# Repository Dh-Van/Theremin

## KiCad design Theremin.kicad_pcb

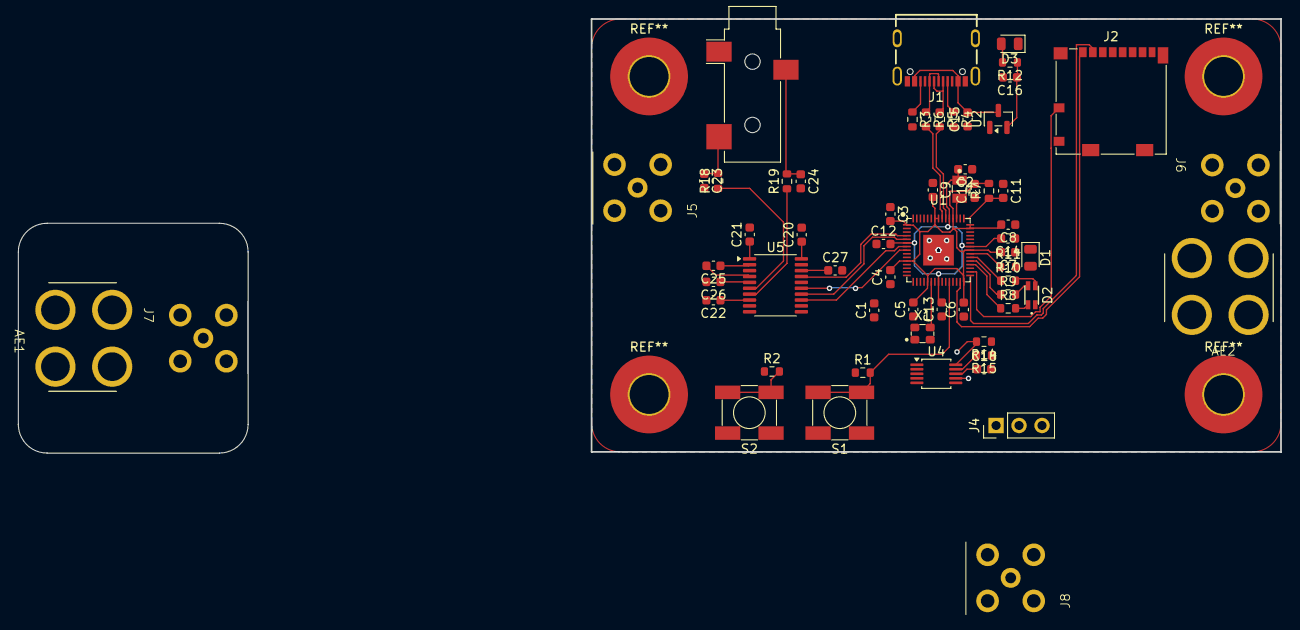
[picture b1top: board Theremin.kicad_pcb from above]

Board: 2 copper layers, 76.2 x 47.9 mm, 62 parts (0 on the bottom side), 54 nets.

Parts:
AE1: Pitch Input; Flat_Antenna_Mount
AE2: Volume Input; Flat_Antenna_Mount
C1, C2, C10, C11, C13: 4.7µF; C_0603_1608Metric
C3, C4, C5, C6, C7, C8, C9, C12, C14: 0.1µF; C_0603_1608Metric
C15, C16: 10µF; C_0603_1608Metric
C18, C27: 1uF; C_0603_1608Metric
C20, C21, C22: 10uF; C_0603_1608Metric
C23, C24: 2.2nF; C_0603_1608Metric
C25, C26: 2.2uF; C_0603_1608Metric
D1: LED; D_0805_2012Metric
D2: IN-S85TATRGB
D3: PWR; D_0805_2012Metric
J1: USB4105-GF-A
J2: Micro_SD_Card_Det2; microSD_HC_Molex_104031-0811
J4: DEBUG; PinHeader_1x03_P2.54mm_Vertical
J5, J6, J7, J8: Conn_Coaxial; Coax_Connector_Right_Angle
J9: AudioJack3; Jack_3.5mm_CUI_SJ-3523-SMT_Horizontal
L1: 3.3µH; AOTA-B201610S3R3-101-T
R1, R2, R3, R4, R9: 5.1K; R_0603_1608Metric
R5, R6: 27Ω; R_0603_1608Metric
R7: 33Ω; R_0603_1608Metric
R8, R10, R11, R12: 1K; R_0603_1608Metric
R14, R15: 3.7kΩ; R_0603_1608Metric
R18, R19: 470Ω; R_0603_1608Metric
S1: RST; TL3301AFxxxxJ
S2: BOOT; TL3301NFxxxxJ
U1: RP2354A; RP2350A_QFN-60_EP_7.75x7.75_Pitch0.4mm
U2: MCP1702T-3302E_CB; SOT-23
U4: FDC1004DGS; TSSOP-10_3x3mm_P0.5mm
U5: PCM5102A; TSSOP-20_4.4x6.5mm_P0.65mm
X1: IQXO-791_12MHz; IQXO-791

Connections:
+1V1: C2.2, C12.2, C13.2, C14.2, L1.1, U1.6 (DVDD), U1.23 (DVDD), U1.39 (DVDD), U1.50 (VREG_FB)
+3V3: C1.2, C3.2, C4.2, C5.2, C6.2, C7.2, C8.2, C9.2, C10.2, C16.1, C18.1, C20.1, C21.1, C22.1, D2.3, J2.4 (VDD), R1.1, R2.1, R7.2, R12.1, R14.1, R15.1, U1.1 (IOVDD), U1.11 (IOVDD), U1.20 (IOVDD), U1.30 (IOVDD), U1.38 (IOVDD), U1.44 (ADC_AVDD), U1.45 (IOVDD), U1.49 (VREG_VIN), U1.53 (USB_OTP_VDD), U1.54 (QSPI_IOVDD), U2.2 (VOUT), U4.8 (VDD), U5.1 (CPVDD), U5.8 (AVDD), U5.20 (DVDD), X1.4 (VS)
+5V: C15.2, J1.A4B9 (VBUS), J1.B4A9 (VBUS), U2.3 (VIN)
/Microcontroller/BOOT: R2.2, S2.2, U1.60 (~QSPI_CS)
/Microcontroller/GPIO14: J2.5 (CLK), U1.18 (GPIO14)
/Microcontroller/GPIO15: J2.3 (CMD), U1.19 (GPIO15)
/Microcontroller/GPIO16: J2.7 (DAT0), U1.27 (GPIO16)
/Microcontroller/GPIO17: J2.8 (DAT1), U1.28 (GPIO17)
/Microcontroller/GPIO18: J2.1 (DAT2), U1.29 (GPIO18)
/Microcontroller/GPIO19: J2.2 (DAT3/CD), U1.31 (GPIO19)
/Microcontroller/GPIO20: J2.9 (DET_B), U1.32 (GPIO20)
/Microcontroller/GPIO22: R8.1, U1.34 (GPIO22)
/Microcontroller/GPIO23: R9.1, U1.35 (GPIO23)
/Microcontroller/GPIO24: R10.1, U1.36 (GPIO24)
/Microcontroller/GPIO25: R11.1, U1.37 (GPIO25)
/Microcontroller/RUN: R1.2, S1.2, U1.26 (RUN)
/Microcontroller/SWCLK: J4.1, U1.24 (SWCLK)
/Microcontroller/SWDIO: J4.3, U1.25 (SWDIO)
GND: C1.1, C2.1, C3.1, C4.1, C5.1, C6.1, C7.1, C8.1, C9.1, C10.1, C11.1, C12.1, C13.1, C14.1, C15.1, C16.2, C18.2, C20.2, C21.2, C22.2, C23.2, C24.2, C26.2, C27.2, D1.1 (K), D3.1 (K), J1.A1B12 (GND), J1.B1A12 (GND), J1.S1 (SHELL), J1.S2 (SHELL), J1.S3 (SHELL), J1.S4 (SHELL), J2.6 (VSS), J2.10 (DET_A), J2.SH (SHIELD), J4.2, J9.S, R3.2, R4.2, S1.1, S2.1, U1.47 (VREG_PGND), U1.61 (GND), U2.1 (GND), U4.7 (GND), U5.3 (CPGND), U5.9 (AGND), U5.10 (DEMP), U5.11 (FLT), U5.12 (SCK), U5.16 (FMT), U5.19 (DGND), X1.2 (GND)
GNDREF: J7.2 (Ext), J8.2 (Ext)
GPIO2: U1.4 (GPIO2), U5.17 (XSMT)
GPIO3: U1.5 (GPIO3), U5.14 (DIN)
GPIO4: U1.7 (GPIO4), U5.13 (BCK)
GPIO5: U1.8 (GPIO5), U5.15 (LRCK)
GPIO6: R14.2, U1.9 (GPIO6), U4.10 (SDA)
GPIO7: R15.2, U1.10 (GPIO7), U4.9 (SCL)
unnamed: AE1.1 (A_1), J7.1 (In)
unnamed: AE2.1 (A_1), J8.1 (In)
unnamed: C23.1, J9.T, R18.2
unnamed: C24.1, J9.R, R19.2
unnamed: D1.2 (A), R11.2
unnamed: D2.1, R8.2
unnamed: D2.2, R9.2
unnamed: D2.4, R10.2
unnamed: D3.2 (A), R12.2
unnamed: J1.A5 (CC1), R4.1
unnamed: J1.B5 (CC2), R3.1
unnamed: J1.A6 (D+), J1.B6 (D+), R6.1
unnamed: J1.A7 (D-), J1.B7 (D-), R5.1
unnamed: J5.2 (Ext), U4.1 (SHLD1)
unnamed: J5.1 (In), U4.2 (CIN1)
unnamed: J6.2 (Ext), U4.6 (SHLD2)
unnamed: J6.1 (In), U4.5 (CIN4)
unnamed: R6.2, U1.52 (USB_D+)
unnamed: R5.2, U1.51 (USB_D-)
unnamed: C11.2, R7.1, U1.46 (VREG_AVDD)
unnamed: L1.2, U1.48 (VREG_LX)
unnamed: U1.21 (XIN), X1.3 (OUT)
unnamed: C25.2, U5.4 (CAPM)
unnamed: C25.1, U5.2 (CAPP)
unnamed: C27.1, U5.18 (LDOO)
unnamed: R18.1, U5.6 (OUTL)
unnamed: R19.1, U5.7 (OUTR)
unnamed: C26.1, U5.5 (VNEG)
